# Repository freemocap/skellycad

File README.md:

# SkellyCAD

CAD, eye-tracker hardware, camera electronics and learning projects.
Start with a project below; its README distinguishes selected assemblies,
review candidates and available print packages.

| Project | Start here |
| --- | --- |
| Eye trackers | [Mouse, rat, marmoset and human](designs/eye-tracker/README.md) |
| Camera modules | [Pupil reference and camera development](designs/cameras/README.md) |
| Capture enclosure | [Frame and capture studies](designs/enclosure/README.md) |
| UltraSkelly mounts | [Camera bracket and Pi 5 stack mount](designs/ultraskelly/README.md) |
| Preserved Mouse Hats | [Historical designs and replay](designs/mouse-hats/README.md) |
| CAD Foundations | [FreeCAD lessons](designs/cad-foundations/README.md) |
| KiCad Foundations | [Electronics lessons](designs/kicad-foundations/README.md) |

[Working guide](docs/organization-guide.md) · [Setup and validation](docs/development.md) ·
[Version control](docs/version-control.md) · [Citations](CITATIONS.md)

The preferred Pupil geometry is the [complete R08 module](designs/cameras/pupil-core-eye/README.md).
Historical assemblies retain their pinned geometry and matched parts.

[Repository cleanup plan](docs/repository-organization.md) ·
[Cleanup and preservation record](docs/migration/repo-cleanup-2026-10-31/README.md) ·
[Original import record](docs/migration/README.md)

Local runtimes stay in `.cad-tools/`; working runs go to `generated/`.
The original `old-cad-playground/` remains untouched for the user's migration review.

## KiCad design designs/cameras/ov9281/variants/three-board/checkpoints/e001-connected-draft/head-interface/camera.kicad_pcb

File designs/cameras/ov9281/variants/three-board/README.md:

# OV9281 three-board

**E01** is a connected electrical draft with unrouted placement and a matched mechanical assembly. It is not accepted for manufacture.

- [Source](src) contains the retained implementation for this configuration.
- [Matched E01 files](checkpoints/e001-connected-draft).
- [Native complete assembly](checkpoints/e001-connected-draft/THREE-BOARD-E01.FCStd) · [Selection/review record](review-model.json).

Use [the working guide](../../../../../docs/organization-guide.md) for isolated replay. Historical commands retain their original paths; run them in the prepared workspace. Use `--current --source designs/cameras/ov9281/variants/three-board/src` when preparing a fresh workspace to include edits from this variant's `src/`.

Keep the native assembly, matching parts, electronics contracts and validation scope together. A saved model or successful geometry check does not demonstrate physical fit.

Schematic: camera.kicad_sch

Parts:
C7, C8, C10, C12, C13, C18, C19, C21, C33, C401, C403, C405, C423, C424, C425, C426: 1u; C_0603_1608Metric; MPN GRM188R71C105KA12D
C9, C14, C15, C16, C17, C20, C408, C411, C414, C417, C418: 100n; C_0402_1005Metric; MPN GRM155R71C104KA88D
C402, C404, C406, C409, C412, C415: 10n; C_0402_1005Metric; MPN GRM155R71C103KA01D
C407, C410, C413: 10u; C_0805_2012Metric; MPN GRM21BR61A106KE19L
C416: 22n; C_0402_1005Metric; MPN GRM155R71H223KA12D
C419, C420: 100n/50V; C_0402_1005Metric; MPN GRM155R71H104KE14D
C421: 4.7u; C_0603_1608Metric; MPN GRM188R61A475KE15D
C422: 22u; C_0805_2012Metric; MPN GRM21BR61A226ME44L
D201, D202: AP1608F3C; Kingbright_AP1608F3C_R09; MPN AP1608F3C
D203, D204: TPD1E01B04 / 0.20pF typ; D_0402_1005Metric; MPN TPD1E01B04DPYR
FB401, FB402, FB403: 120R@100MHz; L_0603_1608Metric; MPN BLM18SG121TN1D
J201: TETHER: 1=5V 2=N 3=P 4=GND; NOT USB; JST_SH_SM04B-SRSS-TB_1x04-1MP_P1.00mm_Horizontal; MPN SM04B-SRSS-TB(LF)(SN)
L1, L2, L3: 3.3u; L_0805_2012Metric; MPN MLP2012S3R3MT0S1
L202: 2.2u / 3.3 A Isat; Murata_DFE252012F_R11; MPN DFE252012F-2R2M=P2
Q201: PMZB200UNE; SOT-883; MPN PMZB200UNEYL
R7: 0; R_0402_1005Metric; MPN RC0402JR-070RL; not fitted
R8, R9: 0; R_0402_1005Metric; MPN RC0402JR-070RL
R201, R202, R203: 2.2k; R_0402_1005Metric; MPN RC0402FR-072K2L
R204, R407, R409: 100k; R_0402_1005Metric; MPN RC0402FR-07100KL
R401, R402, R405: 10k; R_0402_1005Metric; MPN RC0402FR-0710KL
R403, R404: 4.7k; R_0402_1005Metric; MPN RC0402FR-074K7L
R406: 40.2k; R_0402_1005Metric; MPN RC0402FR-0740K2L
R408: 200k; R_0402_1005Metric; MPN RC0402FR-07200KL
TP201: Shield termination; TestPoint_Pad_1.0x1.0mm; MPN PCB solder land
U1: OV9281; MPN OV09281-H64A
U6: TLV73312PDQNR; Texas_X2SON-4_1x1mm_P0.65mm; MPN TLV73312PDQNR
U7: TLV73328PDQNR; Texas_X2SON-4_1x1mm_P0.65mm; MPN TLV73328PDQNR
U201: DS90UB953-Q1; TI_RHB0032P_E01; MPN DS90UB953TRHBRQ1
U202: TLV62569DRLR; TI_DRL0006A_R11; MPN TLV62569DRLR
Y1: SG-210STF 24.0000ML; Epson_SG210STF_2.5x2.0mm_R09; MPN X1G004171003100

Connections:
CAM_L_CLK_N: U1.H4 (MDCN), U201.6 (CSI_CLKN)
CAM_L_CLK_P: U1.G4 (MDCP), U201.5 (CSI_CLKP)
CAM_L_D0_N: U1.H3 (MDN0), U201.4 (CSI_D0N)
CAM_L_D0_P: U1.G3 (MDP0), U201.3 (CSI_D0P)
CAM_L_D1_N: U1.F5 (MD1N), U201.2 (CSI_D1N)
CAM_L_D1_P: U1.G5 (MDP1), U201.1 (CSI_D1P)
CAM_NRST_1V8: R401.1, U1.A5 (XSHUTDOWN), U201.17 (GPIO0)
GND: C7.2, C8.2, C9.2, C10.2, C12.2, C13.2, C14.2, C15.2, C16.2, C17.2, C18.2, C19.2, C20.2, C21.2, C33.2, C401.2, C402.2, C403.2, C404.2, C405.2, C406.2, C407.2, C408.2, C409.2, C410.2, C411.2, C412.2, C413.2, C414.2, C415.2, C417.2, C418.2, C421.2, C422.2, C423.2, C424.2, C425.2, C426.2, D203.2 (IO_GND), D204.2 (IO_GND), J201.4, Q201.2 (S), R8.2, R204.2, R401.2, R402.2, R405.2, R406.2, R409.2, TP201.1, U1.A3 (DOGND), U1.A7 (DOGND), U1.B2 (DOGND), U1.C8 (AGND), U1.D2 (AGND), U1.E3 (EGND), U1.E5 (EGND), U1.E6 (TM), U1.F1 (DOGND), U1.F4 (DOGND), U1.F6 (DOGND), U1.F8 (AGND), U1.G2 (DOGND), U1.H7 (AGND), U6.2 (GND), U6.5 (EP), U7.2 (GND), U7.5 (EP), U201.7 (RES0), U201.33 (EP), U202.2 (GND), Y1.2 (GND)
H1V2: C423.1, L1.1, U6.1 (VOUT)
H1V8: C33.1, C422.1, C424.1, FB401.1, FB402.1, FB403.1, L2.1, L202.2, R403.1, R404.1, R407.1, R408.1, U6.3 (EN), U6.4 (VIN), Y1.1 (EN), Y1.4 (VDD)
H2V8: C425.1, L3.1, U7.1 (VOUT)
H5V: C421.1, C426.1, J201.1, R201.1, R202.1, U7.3 (EN), U7.4 (VIN), U202.3 (VIN), U202.5 (EN)
IR_A1: D201.2 (A), R201.2
IR_A2: D202.2 (A), R202.2
IR_GATE: Q201.1 (G), R203.2, R204.1
IR_K: D201.1 (K), D202.1 (K), Q201.3 (D)
LINK_N: C420.2, D204.1 (IO), J201.2
LINK_P: C419.2, D203.1 (IO), J201.3
M1_AVDD: C18.1, C19.1, C20.1, L3.2, R9.2, U1.B8 (AVDD), U1.C1 (AVDD), U1.G7 (AVDD), U1.G8 (AVDD)
M1_CAM_SCL_1V8: R403.2, U1.E4 (SCL), U201.24 (I2C_SCL)
M1_CAM_SDA_1V8: R404.2, U1.A4 (SDA), U201.23 (I2C_SDA)
M1_DOVDD: C13.1, C15.1, C16.1, L2.2, R7.1, U1.B7 (DOVDD), U1.D3 (DOVDD), U1.H2 (DOVDD), U1.H6 (DOVDD)
M1_DVDD: C9.1, C12.1, C14.1, L1.2, U1.A2 (DVDD), U1.B1 (DVDD), U1.B3 (DVDD), U1.C5 (DVDD), U1.D8 (DVDD), U1.F2 (DVDD), U1.F3 (EVDD), U1.G1 (DVDD), U1.G6 (DVDD), U1.H5 (EVDD)
M1_MCLK: U1.E2 (XVCLK), Y1.3 (OUT)
M1_PVDD: C17.1, R9.1, U1.D5 (PVDD)
M1_SID: R7.2, R8.1, U1.E1 (SID)
M1_VH: C21.1, U1.E8 (VH)
M1_VN1: C7.1, U1.D7 (VN1)
M1_VN2: C8.1, U1.E7 (VN2)
M1_VN3: C10.1, U1.F7 (VN3)
M1_VSYNC_1V8_M: R402.1, U1.B5 (FSIN/VSYNC)
SER_DOUT_N: C420.1, U201.13 (DOUT_N)
SER_DOUT_P: C419.1, U201.14 (DOUT_P)
SER_DRV_CAP: C410.1, C411.1, C412.1, U201.15 (VDDDRV_CAP)
SER_D_CAP: C413.1, C414.1, C415.1, U201.26 (VDDD_CAP)
SER_IDX: R406.1, U201.19 (CLK_OUT_IDX)
SER_LED_PWM: R203.1, U201.18 (GPIO1)
SER_LPF1: C416.1, U201.9 (LPF1)
SER_LPF2: C417.1, U201.12 (LPF2)
SER_MODE: R405.1, U201.21 (MODE)
SER_PDB: C418.1, R407.2, U201.8 (PDB)
SER_PLL_CAP: C407.1, C408.1, C409.1, U201.10 (VDDPLL_CAP)
SER_VDDD: C401.1, C402.1, FB401.2, U201.25 (VDDD)
SER_VDDDRV: C403.1, C404.1, FB402.2, U201.16 (VDDDRV)
SER_VDDPLL: C405.1, C406.1, C416.2, FB403.2, U201.11 (VDDPLL)
U202_FB: R408.2, R409.1, U202.1 (FB)
U202_SW: L202.1, U202.4 (SW)

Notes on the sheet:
THREE-BOARD E01 / HEAD-INTERFACE / CONNECTED ELECTRICAL DRAFT
Pins and matching net labels define connectivity. Unrouted; procurement, optics, cable and hardware qualification remain open.
Active circuitry
Supporting parts / references match BOM and PCB / no implicit connections

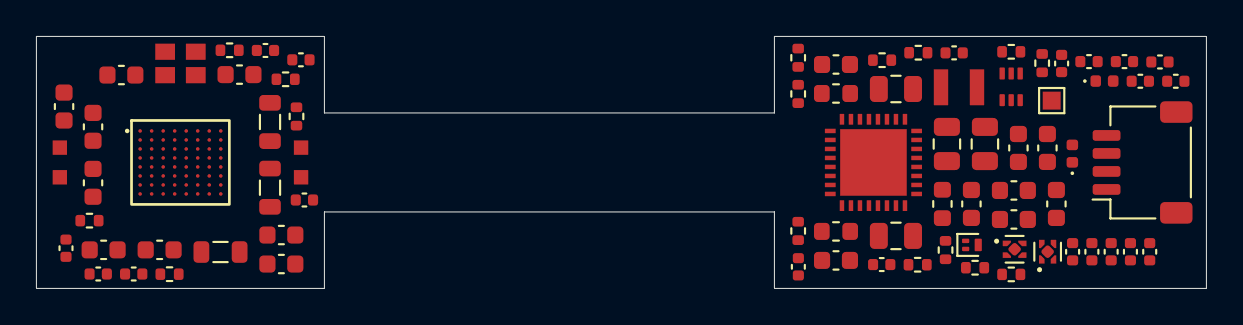
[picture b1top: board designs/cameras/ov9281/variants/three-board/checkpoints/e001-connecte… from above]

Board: 4 copper layers, 65.0 x 14.0 mm, 77 parts (0 on the bottom side), 47 nets, no tracks yet.

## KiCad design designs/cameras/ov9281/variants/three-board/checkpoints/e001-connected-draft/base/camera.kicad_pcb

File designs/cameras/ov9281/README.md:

# OV9281 camera development

| Configuration | Status and entry point |
| --- | --- |
| [Slim-flex](variants/slim-flex/README.md) | Preserved R11 routed candidate; R08 remains the historical electrical selection. |
| [Three-board](variants/three-board/README.md) | E01 connected electrical draft and matched mechanical assembly; boards remain unrouted. |

Neither configuration is an accepted manufacturing release or demonstrated
working camera. The nominal mass targets and unresolved electrical/optical gates
remain in the variant records.

[Shared earlier investigations](history/README.md) · [Supplied references](references) ·
[Pre-cleanup overview](history/overview-before-cleanup.md)

[Shared utilities](shared/README.md) · [Development roadmap](ROADMAP.md)

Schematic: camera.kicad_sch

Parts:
C101, C102: 16p; C_0402_1005Metric; MPN GRM1555C1H160JA01D
C103, C110, C111, C112, C113, C114, C115, C116, C117, C118, C119, C120, C121, C122, C128, C129, C130, C132, C135, C607, C612, C618, C620, C622, C624, C627: 100n; C_0402_1005Metric; MPN GRM155R71C104KA88D
C104, C125, C126, C127, C133, C604, C609, C615, C628, C629: 1u; C_0603_1608Metric; MPN GRM188R71C105KA12D
C105, C108, C136, C601, C602, C617, C619, C621, C623: 4.7u; C_0603_1608Metric; MPN GRM188R61A475KE15D
C106, C109, C123, C124, C603: 22u; C_0805_2012Metric; MPN GRM21BR61A226ME44L
C107: 22p; C_0402_1005Metric; MPN GRM1555C1H220JA01D
C131, C134, C605, C608, C610, C613, C616: 10n; C_0402_1005Metric; MPN GRM155R71C103KA01D
C606, C611, C614: 10u; C_0805_2012Metric; MPN GRM21BR61A106KE19L
C625, C626: 100n/50V; C_0402_1005Metric; MPN GRM155R71H104KE14D
D301, D302: TPD1E01B04 / 0.20pF typ; D_0402_1005Metric; MPN TPD1E01B04DPYR
FB601, FB602, FB603: 120R@100MHz; L_0603_1608Metric; MPN BLM18SG121TN1D
J101: USB / JST SH / 1VBUS 2DM 3DP 4GND; JST_SH_SM04B-SRSS-TB_1x04-1MP_P1.00mm_Horizontal; MPN SM04B-SRSS-TB(LF)(SN)
J103: PROGRAM / RESET pads; ProgrammingPads_5x1mm_P1.5mm; MPN PCB programming lands
J301: TETHER: 1=5V 2=N 3=P 4=GND; NOT USB; JST_SH_SM04B-SRSS-TB_1x04-1MP_P1.00mm_Horizontal; MPN SM04B-SRSS-TB(LF)(SN)
L101, L102, L302: 2.2u / 3.3 A Isat; Murata_DFE252012F_R11; MPN DFE252012F-2R2M=P2
Q301, Q302: PMZB200UNE; SOT-883; MPN PMZB200UNEYL
R101, R102, R103, R104, R605, R609, R610, R612, R615: 10k; R_0402_1005Metric; MPN RC0402FR-0710KL
R105, R106: 499k; R_0402_1005Metric; MPN RC0402FR-07499KL
R107: 453k; R_0402_1005Metric; MPN RC0402FR-07453KL
R108, R601, R602, R604, R613, R614: 100k; R_0402_1005Metric; MPN RC0402FR-07100KL
R109, R110: 0; R_0402_1005Metric; MPN RC0402JR-070RL
R111: 4.02k; R_0402_1005Metric; MPN RC0402FR-074K02L
R113, R115, R608: 4.7k; R_0402_1005Metric; MPN RC0402FR-074K7L
R603: 200k; R_0402_1005Metric; MPN RC0402FR-07200KL
R606: 78.7k; R_0402_1005Metric; MPN RC0402FR-0778K7L
R607: 97.6k; R_0402_1005Metric; MPN RC0402FR-0797K6L
R611: 80.6k; R_0402_1005Metric; MPN RC0402FR-0780K6L
TP301: Tether shield; TestPoint_Pad_1.0x1.0mm; MPN PCB solder land
TP302: REGULATED 5V INPUT; TestPoint_Pad_1.0x1.0mm; MPN PCB solder land
TP303: POWER RETURN; TestPoint_Pad_1.0x1.0mm; MPN PCB solder land
U101: ESP32-P4NRW16X / v3.x; ESP32-P4; MPN ESP32-P4NRW16X
U102: W25Q32JVUUIQ / 4 MB; Winbond_USON-8-2EP_3x4mm_P0.8mm_EP0.2x0.8mm; MPN W25Q32JVUUIQ TR
U103, U104, U302: TLV62569DRLR; TI_DRL0006A_R11; MPN TLV62569DRLR
U105: USBLC6-2P6; SOT-666; MPN USBLC6-2P6
U301: DS90UB954-Q1 / internal LDOs; TI_RGZ0048B_E01; MPN DS90UB954TRGZRQ1
U303: TPS2553 / current-limited head power; TI_DRV0006A_E01; MPN TPS2553DRVR
Y101: 40 MHz / CL 10pF; ECS_ECX1637B2_R11; MPN ECS-400-10-37B2-CKM-TR
Y301: SG-210STF 25.0000ML / 1.8V; Epson_SG210STF_2.5x2.0mm_R09; MPN SG-210STF 25.0000ML

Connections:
+3V3: C105.1, C109.1, C110.1, C111.1, C114.1, C115.1, C117.1, C118.1, C120.1, C121.1, C122.1, C123.1, C134.1, C135.1, C136.1, C604.1, C605.1, C609.1, C610.1, L102.2, R102.1, R103.1, R104.1, R107.1, R113.1, R115.1, R608.1, R609.1, R612.1, R615.1, U101.9 (VDD_LP), U101.21 (VDD_IO_0), U101.51 (VDD_USBPHY), U101.62 (VDD_IO_4), U101.75 (VDD_LDO), U101.77 (VDD_DCDCC), U101.85 (VDD_IO_5), U101.96 (VDD_IO_6), U101.101 (VDD_ANA), U101.102 (VDD_BAT), U103.3 (VIN), U301.7 (VDDIO), U301.29 (VDDIO)
B5V: C601.1, C602.1, C628.1, TP302.1, U104.3 (VIN), U104.5 (EN), U302.3 (VIN), U302.5 (EN), U303.6 (IN)
BASE_SCL: R113.2, U101.7 (GPIO7), U301.2 (SCL)
BASE_SDA: R115.2, U101.8 (GPIO8), U301.1 (SDA)
CAM_L_CLK_N: U101.45 (CSI_CLKN), U301.11 (CSI_CLK0N)
CAM_L_CLK_P: U101.44 (CSI_CLKP), U301.12 (CSI_CLK0P)
CAM_L_D0_N: U101.42 (CSI_DATAN0), U301.13 (CSI_D0N)
CAM_L_D0_P: U101.43 (CSI_DATAP0), U301.14 (CSI_D0P)
CAM_L_D1_N: U101.46 (CSI_DATAN1), U301.15 (CSI_D1N)
CAM_L_D1_P: U101.47 (CSI_DATAP1), U301.16 (CSI_D1P)
FLASH_CLK: U101.32 (FLASH_CK), U102.6 (CLK)
FLASH_CS: R101.2, U101.27 (FLASH_CS), U102.1 (~CS)
FLASH_D: U101.33 (FLASH_D), U102.5 (DI/IO_{0})
FLASH_HOLD: U101.31 (FLASH_HOLD), U102.7 (~HOLD/~RESET/IO_{3})
FLASH_Q: U101.28 (FLASH_Q), U102.2 (DO/IO_{1})
FLASH_WP: U101.29 (FLASH_WP), U102.3 (~WP/IO_{2})
GND: C101.2, C102.2, C103.2, C104.2, C105.2, C106.2, C108.2, C109.2, C110.2, C111.2, C112.2, C113.2, C114.2, C115.2, C116.2, C117.2, C118.2, C119.2, C120.2, C121.2, C122.2, C123.2, C124.2, C125.2, C126.2, C127.2, C128.2, C129.2, C130.2, C131.2, C132.2, C133.2, C134.2, C135.2, C136.2, C601.2, C602.2, C603.2, C604.2, C605.2, C606.2, C607.2, C608.2, C609.2, C610.2, C611.2, C612.2, C613.2, C614.2, C615.2, C616.2, C617.2, C618.2, C619.2, C620.2, C621.2, C622.2, C623.2, C624.2, C627.2, C628.2, C629.2, D301.2 (IO_GND), D302.2 (IO_GND), J101.4, J103.1, J301.4, Q301.2 (S), Q302.2 (S), R106.2, R108.2, R111.2, R601.2, R602.2, R604.2, R605.2, R607.2, R611.2, R614.2, TP301.1, TP303.1, U101.105 (GND), U102.4 (GND), U102.9 (EP), U103.2 (GND), U104.2 (GND), U105.2 (GND), U301.6 (BISTEN), U301.44 (RES), U301.46 (VDD_SEL), U301.49 (EP), U302.2 (GND), U303.5 (GND), U303.7 (EP), Y101.2 (G), Y101.4 (G), Y301.2 (GND)
LINK_N: C626.1, D302.1 (IO), J301.2
LINK_P: C625.1, D301.1 (IO), J301.3
P4_BOOT: J103.4, R103.2, U101.66 (GPIO35)
P4_CSI_REXT: R111.1, U101.48 (CSI_REXT)
P4_DOWNLOAD_ENABLE: R104.2, U101.68 (GPIO36)
P4_EN: C104.1, J103.5, R102.2, U101.103 (CHIP_PU)
P4_EN_DCDC: U101.79 (EN_DCDC), U103.5 (EN)
P4_FB: C107.2, R105.2, R106.1, U101.78 (FB_DCDC), U103.1 (FB)
P4_FLASH_VDD: C103.1, C125.1, C128.1, R101.1, U101.30 (VDD_FLASH_IO), U101.71 (VDDO_FLASH), U102.8 (VCC)
P4_LDO4_UNUSED: C127.1, U101.74 (VDDO_4)
P4_MIPI_2V5: C131.1, C132.1, C133.1, U101.41 (VDD_MIPI_DPHY), U101.73 (VDDO_3)
P4_PSRAM_VDD: C126.1, C129.1, C130.1, U101.59 (VDD_PSRAM_0), U101.67 (VDD_PSRAM_1), U101.72 (VDDO_PSRAM)
P4_SW: L101.1, U103.4 (SW)
P4_UART_RX: J103.3, U101.70 (GPIO38)
P4_UART_TX: J103.2, U101.69 (GPIO37)
P4_VDD_HP: C106.1, C107.1, C112.1, C113.1, C116.1, C119.1, C124.1, L101.2, R105.1, U101.26 (VDD_HP_0), U101.54 (VDD_HP_1), U101.76 (VDD_HP_2), U101.91 (VDD_HP_3)
P4_XTAL_N: C102.1, U101.99 (XTAL_N), Y101.3
P4_XTAL_P: C101.1, U101.100 (XTAL_P), Y101.1
RX1V8: C603.1, C627.1, FB601.1, FB602.1, FB603.1, L302.2, R603.1, R606.1, R610.1, Y301.4 (VDD)
RX_CLK_DISABLE: Q301.1 (G), R609.2, U101.10 (GPIO9)
RX_CLK_OE: Q301.3 (D), R610.2, Y301.1 (EN)
RX_CSI_CAP: C619.1, C620.1, U301.20 (VDD11_CSI)
RX_D_CAP: C617.1, C618.1, U301.3 (VDD11_D)
RX_FPD0_CAP: C621.1, C622.1, U301.43 (VDD11_FPD0)
RX_FPD1_CAP: C623.1, C624.1, U301.34 (VDD11_FPD1)
RX_IDX: R605.1, U301.35 (IDX)
RX_INT_N: R608.2, U101.14 (GPIO13), U301.25 (GPIO3_INTB)
RX_IN_N: C626.2, U301.42 (RIN0N)
RX_IN_P: C625.2, U301.41 (RIN0P)
RX_LOCK: U101.11 (GPIO10), U301.48 (LOCK)
RX_MODE: R606.2, R607.1, U301.37 (MODE)
RX_PASS: U101.12 (GPIO11), U301.47 (PASS)
RX_PDB: R601.1, U101.6 (GPIO6), U301.30 (PDB)
RX_REFCLK: U301.5 (XIN_REFCLK), Y301.3 (OUT)
RX_VDD18_CSI: C615.1, C616.1, FB601.2, U301.17 (VDD18_CSI)
RX_VDD18_FPD: C606.1, C607.1, C611.1, C612.1, FB602.2, U301.31 (VDD18_FPD1), U301.40 (VDD18_FPD0)
RX_VDD18_P: C608.1, C613.1, C614.1, FB603.2, U301.36 (VDD18_P1), U301.45 (VDD18_P0)
SYS_FB: R107.2, R108.1, U104.1 (FB)
SYS_SW: L102.1, U104.4 (SW)
TETHER_5V: C629.1, J301.1, U303.1 (OUT)
TETHER_EN: R602.1, U101.5 (GPIO5), U303.4 (EN)
TETHER_FAULT_N: R612.2, U101.13 (GPIO12), U303.3 (FAULT_N)
TETHER_ILIM: R611.1, U303.2 (ILIM)
U302_FB: R603.2, R604.1, U302.1 (FB)
U302_SW: L302.1, U302.4 (SW)
USB_DM: J101.2, R109.1, U105.1 (I/O1), U105.6 (I/O1)
USB_DM_CHIP: R109.2, U101.49 (USB-DM)
USB_DP: J101.3, R110.1, U105.3 (I/O2), U105.4 (I/O2)
USB_DP_CHIP: R110.2, U101.50 (USB-DP)
USB_PRESENT_N: Q302.3 (D), R615.2, U101.17 (GPIO16/ADC1_CHANNEL0)
USB_VBUS: C108.1, J101.1, R613.1, U105.5 (VBUS)
USB_VBUS_GATE: Q302.1 (G), R613.2, R614.1

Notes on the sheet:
THREE-BOARD E01 / BASE / CONNECTED ELECTRICAL DRAFT
Pins and matching net labels define connectivity. Unrouted; procurement, optics, cable and hardware qualification remain open.
Active circuitry
Supporting parts / references match BOM and PCB / no implicit connections

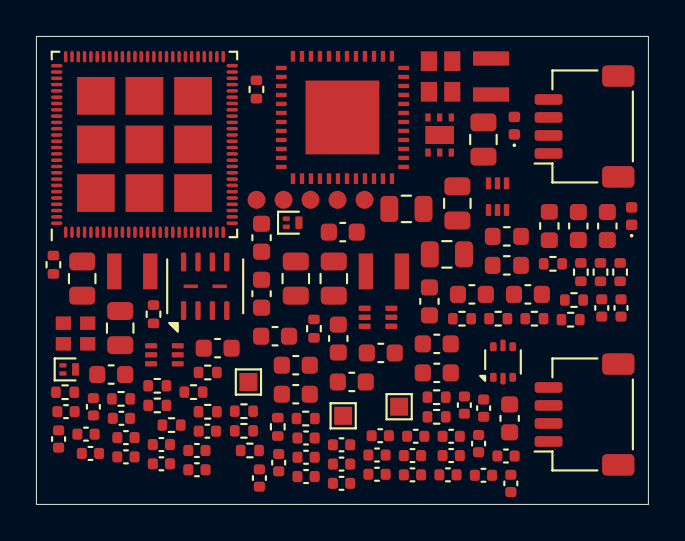
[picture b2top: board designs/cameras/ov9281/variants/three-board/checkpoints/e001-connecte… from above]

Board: 4 copper layers, 34.0 x 26.0 mm, 119 parts (0 on the bottom side), 69 nets, no tracks yet.

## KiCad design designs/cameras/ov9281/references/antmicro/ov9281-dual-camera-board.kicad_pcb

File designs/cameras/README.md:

# Camera catalog

| Camera | Role and status |
| --- | --- |
| [Pupil Core eye](pupil-core-eye/README.md) | Selected complete R08 mock-up, optical datum and retained geometry studies. |
| [Inherited Pupil fit profile](pupil-core-eye-inherited/README.md) | Historical approximate envelope used by preserved assemblies. |
| [OV9281](ov9281/README.md) | Slim-flex and three-board engineering work; no demonstrated working camera. |
| [OG0TC / OC0TC](og0tc/README.md) | Preserved earlier direction, superseded by OV9281 development. |

Use `shared.camera.add_camera` for new Pupil geometry. Keep the complete module
and optical datum together. Existing species checkpoints retain their selections.

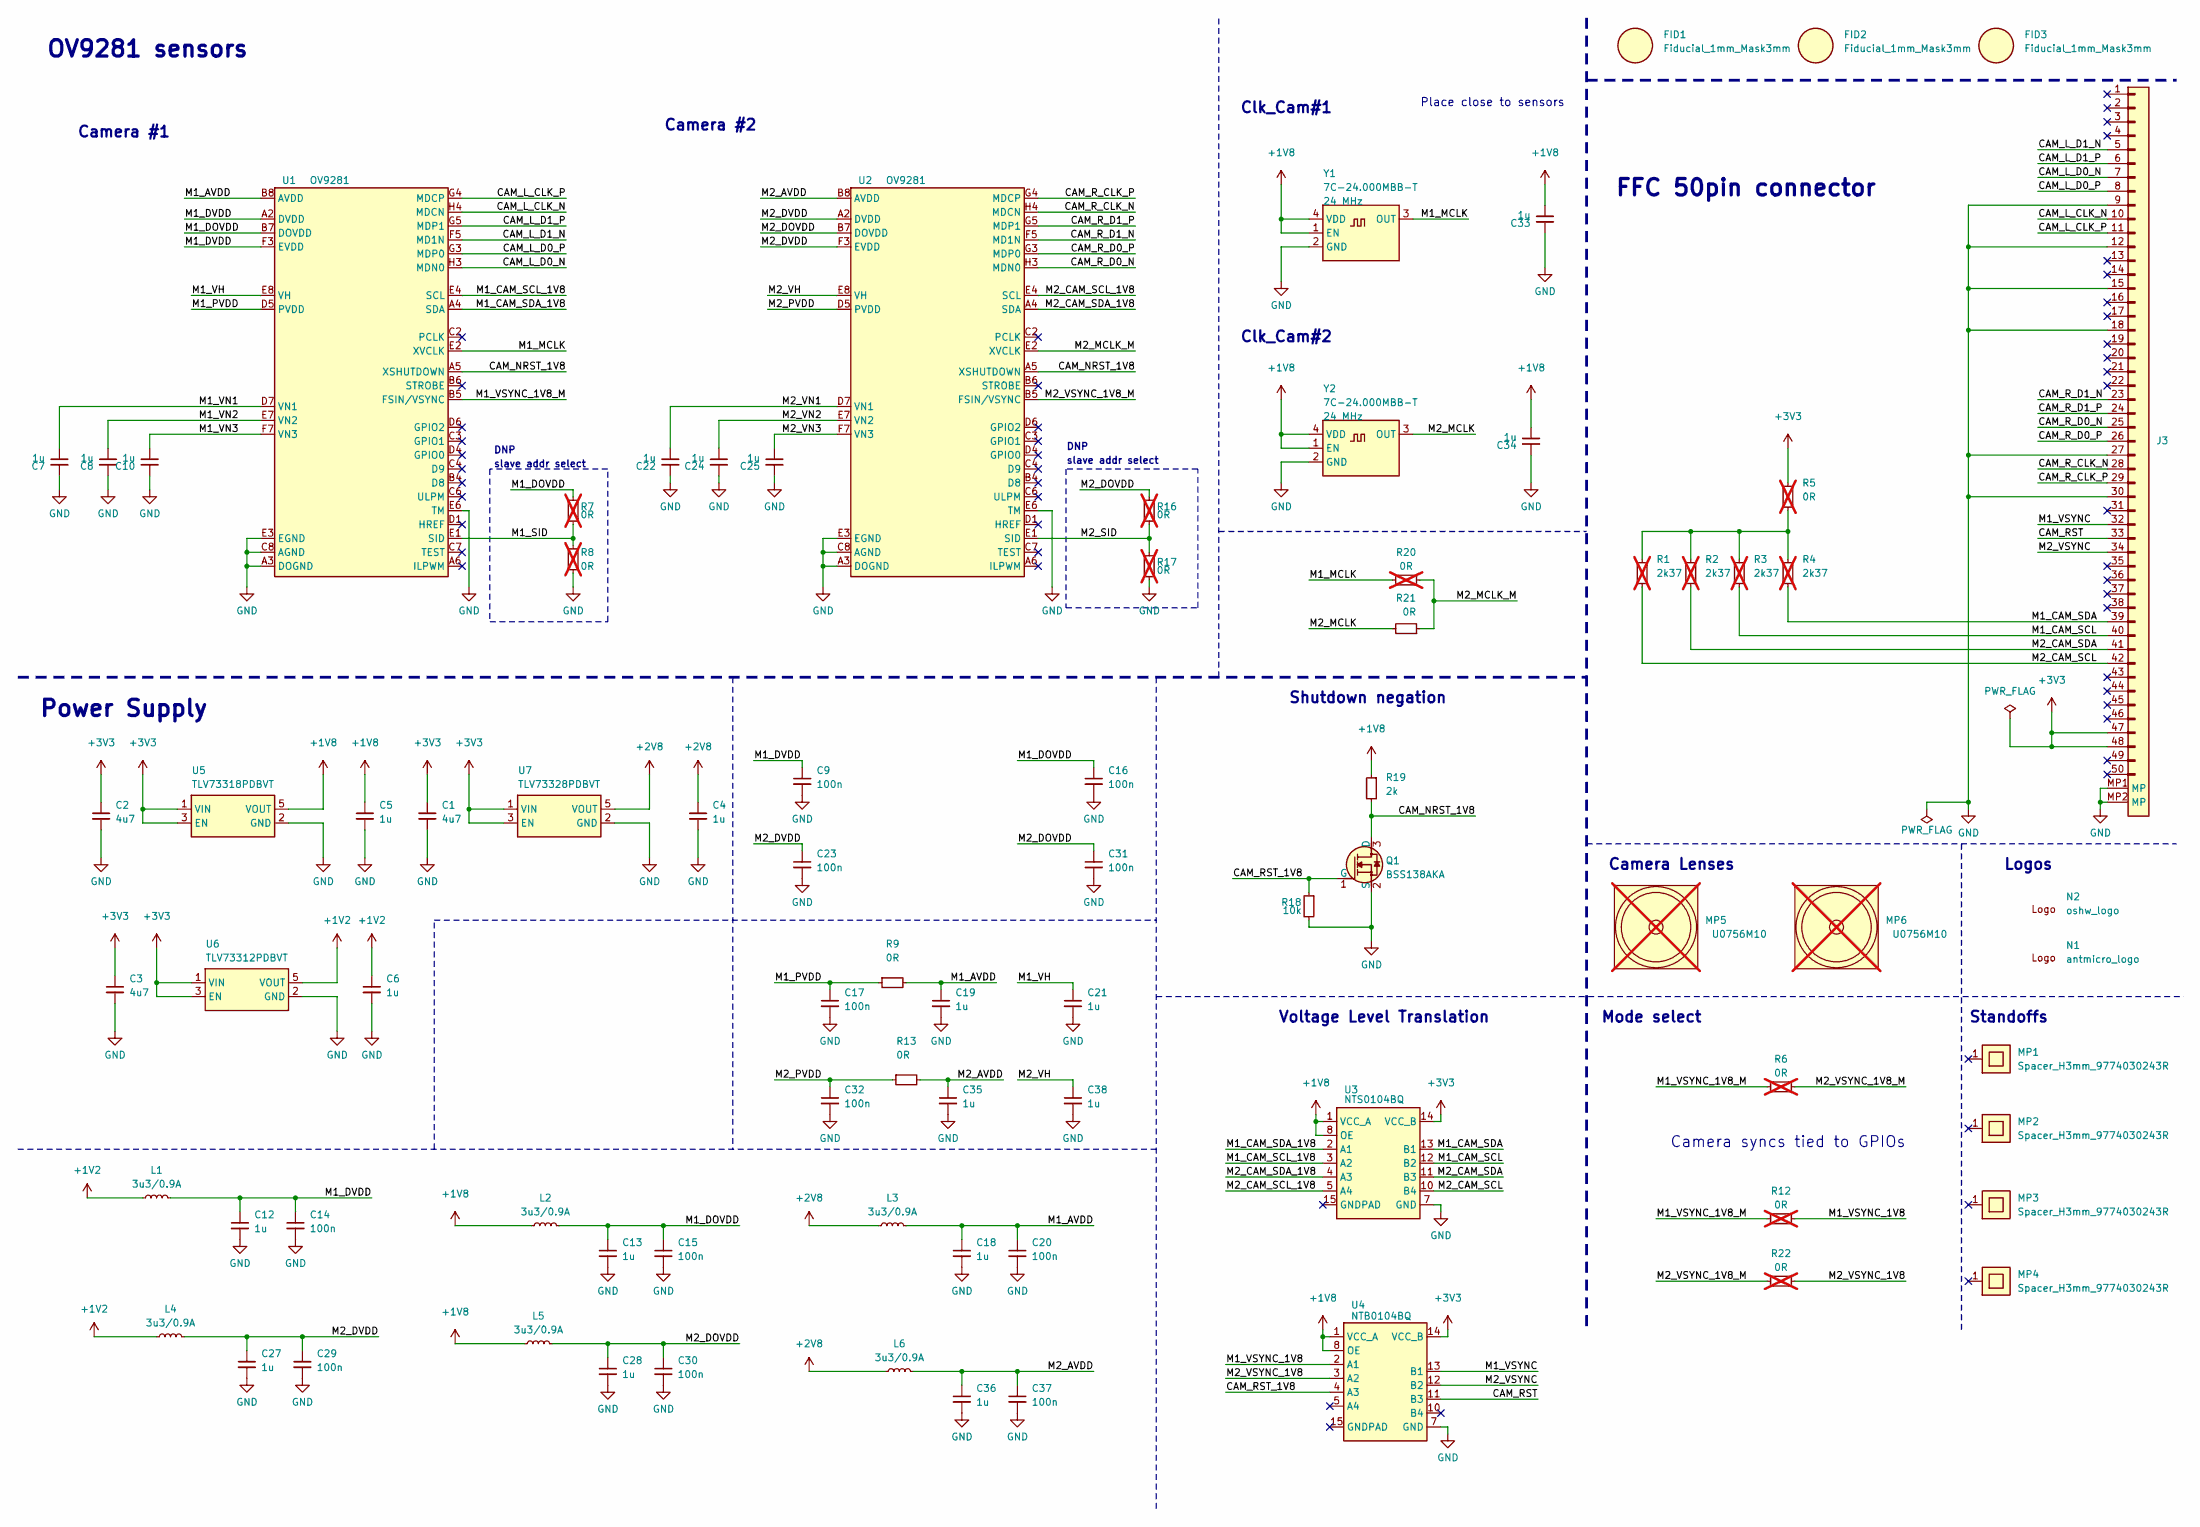
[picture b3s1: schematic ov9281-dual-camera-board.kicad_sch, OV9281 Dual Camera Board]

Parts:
C1, C2, C3: C_4u7_0805; C_0805_2012Metric; MPN 0805X475K250CT
C4, C5, C6, C7, C8, C10, C12, C13, C18, C19, C21, C22, C24, C25, C27, C28, C33, C34, C35, C36, C38: C_1u_0603; C_0603_1608Metric; MPN 0603YD105KAT2A
C9, C14, C15, C16, C17, C20, C23, C29, C30, C31, C32, C37: C_100n_6V3_0402; C_0402_1005Metric; MPN 0402X104K6R3CT
FID1, FID2, FID3: Fiducial_1mm_Mask3mm
J3: Conn_FFC_WE_68715014522_TWO-SIDES; Conn_FFC_WE_68715014x22_ALT; MPN 68715014522
L1, L2, L3, L4, L5, L6: MLP2012S3R3MT; L_0805_2012Metric; MPN MLP2012S3R3MT
MP1, MP2, MP3, MP4: Spacer_H3mm_9774030243R; Spacer_Drill3mm_H3mm_9774030243R; MPN 9774030243R
MP5, MP6: Camera_Lens_20mm; MPN U0756M10; not fitted
N1: antmicro_logo; antmicro-logo_scaled_20mm
N2: oshw_logo; oshw-logo
Q1: BSS138AKA; SOT-23-3; MPN BSS138AKA
R1, R2, R3, R4: R_2k37_0402; R_0402_1005Metric; Tolerance 1%; MPN CR0402-FX-2371GLF; not fitted
R5, R6, R7, R8, R12, R16, R17, R20, R22: R_0R_0402; R_0402_1005Metric; MPN ERJ2GE0R00X; not fitted
R9, R13, R21: R_0R_0402; R_0402_1005Metric; MPN ERJ2GE0R00X
R18: R_10k_0402; R_0402_1005Metric; Tolerance 1%; MPN CR0402-FX-1002GLF
R19: R_2k_0402; R_0402_1005Metric; Tolerance 1%; MPN CR0402-FX-2001GLF
U1, U2: ImageSensor_OV9281; OV9281; MPN OV9281
U3: NTS0104BQ; DHVQFN-14-1EP_2.5x3mm; MPN NTS0104BQ
U4: NTB0104BQ; DHVQFN-14-1EP_2.5x3mm; MPN NTB0104BQ
U5: TLV73318PDBVT; SOT-23-5; MPN TLV73318PDBVT
U6: TLV73312PDBVT; SOT-23-5; MPN TLV73312PDBVT
U7: TLV73328PDBVT; SOT-23-5; MPN TLV73328PDBVT
Y1, Y2: 7C-24.000MBB-T; Oscillator_SMD_TXC_7C_5x3.2x1.2mm; MPN 7C-24.000MBB-T

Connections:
+1V2: C6.1, L1.1, L4.1, U6.5 (VOUT)
+1V8: C5.1, C33.1, C34.1, L2.1, L5.1, R19.1, U3.1 (VCC_A), U3.8 (OE), U4.1 (VCC_A), U4.8 (OE), U5.5 (VOUT), Y1.1 (EN), Y1.4 (VDD), Y2.1 (EN), Y2.4 (VDD)
+2V8: C4.1, L3.1, L6.1, U7.5 (VOUT)
+3V3: C1.1, C2.1, C3.1, J3.47, J3.48, R5.1, U3.14 (VCC_B), U4.14 (VCC_B), U5.1 (VIN), U5.3 (EN), U6.1 (VIN), U6.3 (EN), U7.1 (VIN), U7.3 (EN)
/CAM_L_CLK_N: J3.10, U1.H4 (MDCN)
/CAM_L_CLK_P: J3.11, U1.G4 (MDCP)
/CAM_L_D0_N: J3.7, U1.H3 (MDN0)
/CAM_L_D0_P: J3.8, U1.G3 (MDP0)
/CAM_L_D1_N: J3.5, U1.F5 (MD1N)
/CAM_L_D1_P: J3.6, U1.G5 (MDP1)
/CAM_NRST_1V8: Q1.3 (D), R19.2, U1.A5 (XSHUTDOWN), U2.A5 (XSHUTDOWN)
/CAM_RST: J3.33, U4.11 (B3)
/CAM_RST_1V8: Q1.1 (G), R18.1, U4.4 (A3)
/CAM_R_CLK_N: J3.28, U2.H4 (MDCN)
/CAM_R_CLK_P: J3.29, U2.G4 (MDCP)
/CAM_R_D0_N: J3.25, U2.H3 (MDN0)
/CAM_R_D0_P: J3.26, U2.G3 (MDP0)
/CAM_R_D1_N: J3.23, U2.F5 (MD1N)
/CAM_R_D1_P: J3.24, U2.G5 (MDP1)
/M1_AVDD: C18.1, C19.1, C20.1, L3.2, R9.2, U1.B8 (AVDD), U1.C1 (AVDD), U1.G7 (AVDD), U1.G8 (AVDD)
/M1_CAM_SCL: J3.40, R3.2, U3.12 (B2)
/M1_CAM_SCL_1V8: U1.E4 (SCL), U3.3 (A2)
/M1_CAM_SDA: J3.39, R4.2, U3.13 (B1)
/M1_CAM_SDA_1V8: U1.A4 (SDA), U3.2 (A1)
/M1_DOVDD: C13.1, C15.1, C16.1, L2.2, R7.1, U1.B7 (DOVDD), U1.D3 (DOVDD), U1.H2 (DOVDD), U1.H6 (DOVDD)
/M1_DVDD: C9.1, C12.1, C14.1, L1.2, U1.A2 (DVDD), U1.B1 (DVDD), U1.B3 (DVDD), U1.C5 (DVDD), U1.D8 (DVDD), U1.F2 (DVDD), U1.F3 (EVDD), U1.G1 (DVDD), U1.G6 (DVDD), U1.H5 (EVDD)
/M1_MCLK: R20.2, U1.E2 (XVCLK), Y1.3 (OUT)
/M1_PVDD: C17.1, R9.1, U1.D5 (PVDD)
/M1_SID: R7.2, R8.1, U1.E1 (SID)
/M1_VH: C21.1, U1.E8 (VH)
/M1_VN1: C7.1, U1.D7 (VN1)
/M1_VN2: C8.1, U1.E7 (VN2)
/M1_VN3: C10.1, U1.F7 (VN3)
/M1_VSYNC: J3.32, U4.13 (B1)
/M1_VSYNC_1V8: R12.2, U4.2 (A1)
/M1_VSYNC_1V8_M: R6.1, R12.1, U1.B5 (FSIN/VSYNC)
/M2_AVDD: C35.1, C36.1, C37.1, L6.2, R13.2, U2.B8 (AVDD), U2.C1 (AVDD), U2.G7 (AVDD), U2.G8 (AVDD)
/M2_CAM_SCL: J3.42, R1.2, U3.10 (B4)
/M2_CAM_SCL_1V8: U2.E4 (SCL), U3.5 (A4)
/M2_CAM_SDA: J3.41, R2.2, U3.11 (B3)
/M2_CAM_SDA_1V8: U2.A4 (SDA), U3.4 (A3)
/M2_DOVDD: C28.1, C30.1, C31.1, L5.2, R16.1, U2.B7 (DOVDD), U2.D3 (DOVDD), U2.H2 (DOVDD), U2.H6 (DOVDD)
/M2_DVDD: C23.1, C27.1, C29.1, L4.2, U2.A2 (DVDD), U2.B1 (DVDD), U2.B3 (DVDD), U2.C5 (DVDD), U2.D8 (DVDD), U2.F2 (DVDD), U2.F3 (EVDD), U2.G1 (DVDD), U2.G6 (DVDD), U2.H5 (EVDD)
/M2_MCLK: R21.2, Y2.3 (OUT)
/M2_MCLK_M: R20.1, R21.1, U2.E2 (XVCLK)
/M2_PVDD: C32.1, R13.1, U2.D5 (PVDD)
/M2_SID: R16.2, R17.1, U2.E1 (SID)
/M2_VH: C38.1, U2.E8 (VH)
/M2_VN1: C22.1, U2.D7 (VN1)
/M2_VN2: C24.1, U2.E7 (VN2)
/M2_VN3: C25.1, U2.F7 (VN3)
/M2_VSYNC: J3.34, U4.12 (B2)
/M2_VSYNC_1V8: R22.2, U4.3 (A2)
/M2_VSYNC_1V8_M: R6.2, R22.1, U2.B5 (FSIN/VSYNC)
GND: C1.2, C2.2, C3.2, C4.2, C5.2, C6.2, C7.2, C8.2, C9.2, C10.2, C12.2, C13.2, C14.2, C15.2, C16.2, C17.2, C18.2, C19.2, C20.2, C21.2, C22.2, C23.2, C24.2, C25.2, C27.2, C28.2, C29.2, C30.2, C31.2, C32.2, C33.2, C34.2, C35.2, C36.2, C37.2, C38.2, J3.9, J3.12, J3.15, J3.18, J3.27, J3.30, J3.MP1 (MP), J3.MP2 (MP), Q1.2 (S), R8.2, R17.2, R18.2, U1.A3 (DOGND), U1.A7 (DOGND), U1.B2 (DOGND), U1.C8 (AGND), U1.D2 (AGND), U1.E3 (EGND), U1.E5 (EGND), U1.E6 (TM), U1.F1 (DOGND), U1.F4 (DOGND), U1.F6 (DOGND), U1.F8 (AGND), U1.G2 (DOGND), U1.H7 (AGND), U2.A3 (DOGND), U2.A7 (DOGND), U2.B2 (DOGND), U2.C8 (AGND), U2.D2 (AGND), U2.E3 (EGND), U2.E5 (EGND), U2.E6 (TM), U2.F1 (DOGND), U2.F4 (DOGND), U2.F6 (DOGND), U2.F8 (AGND), U2.G2 (DOGND), U2.H7 (AGND), U3.7 (GND), U4.7 (GND), U5.2 (GND), U6.2 (GND), U7.2 (GND), Y1.2 (GND), Y2.2 (GND)
unnamed: R1.1, R2.1, R3.1, R4.1, R5.2

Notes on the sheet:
Voltage Level Translation
FFC 50pin connector
slave addr select
Power Supply
Place close to sensors
Shutdown negation
DNP
Clk_Cam#2
Camera #1
Camera Lenses
Camera #2
Standoffs
Mode select
Logos
Camera syncs tied to GPIOs
OV9281 sensors
Clk_Cam#1

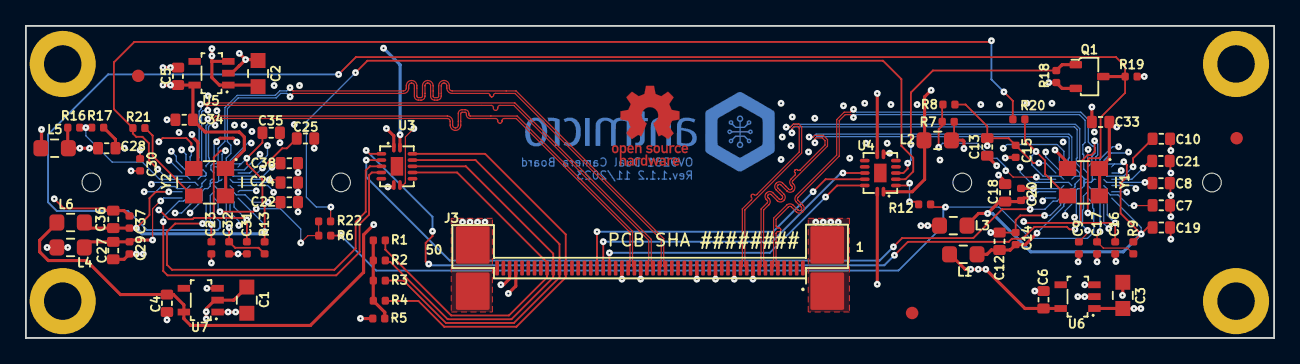
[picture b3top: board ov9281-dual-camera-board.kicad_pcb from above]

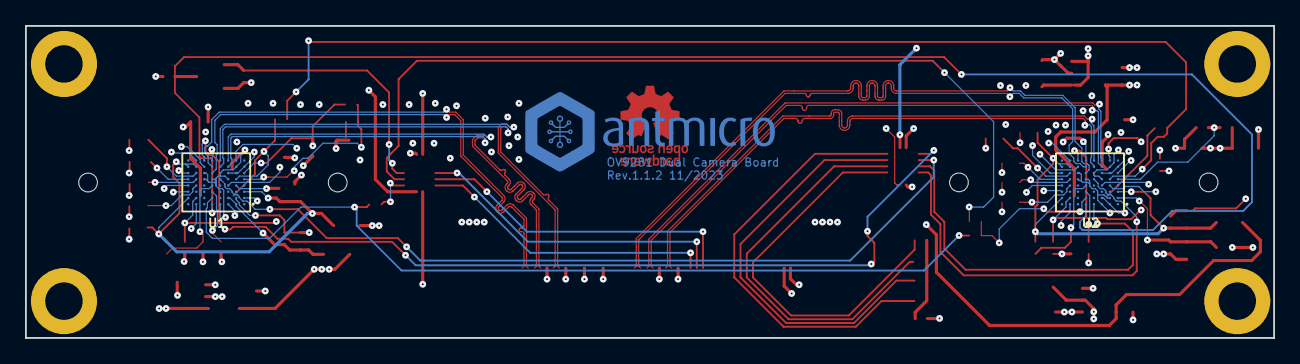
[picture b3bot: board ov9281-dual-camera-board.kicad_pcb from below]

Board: 4 copper layers, 100.0 x 25.0 mm, 82 parts (5 on the bottom side), 56 nets.

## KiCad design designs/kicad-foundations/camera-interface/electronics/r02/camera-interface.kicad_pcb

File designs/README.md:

# Design catalog

Use the [repository project catalog](../README.md) for current entry points.
Eye trackers are grouped by animal and variant. Camera modules have a shared
catalog; enclosure and UltraSkelly mount work are independent. Mouse Hats and
both foundations courses retain their established paths.

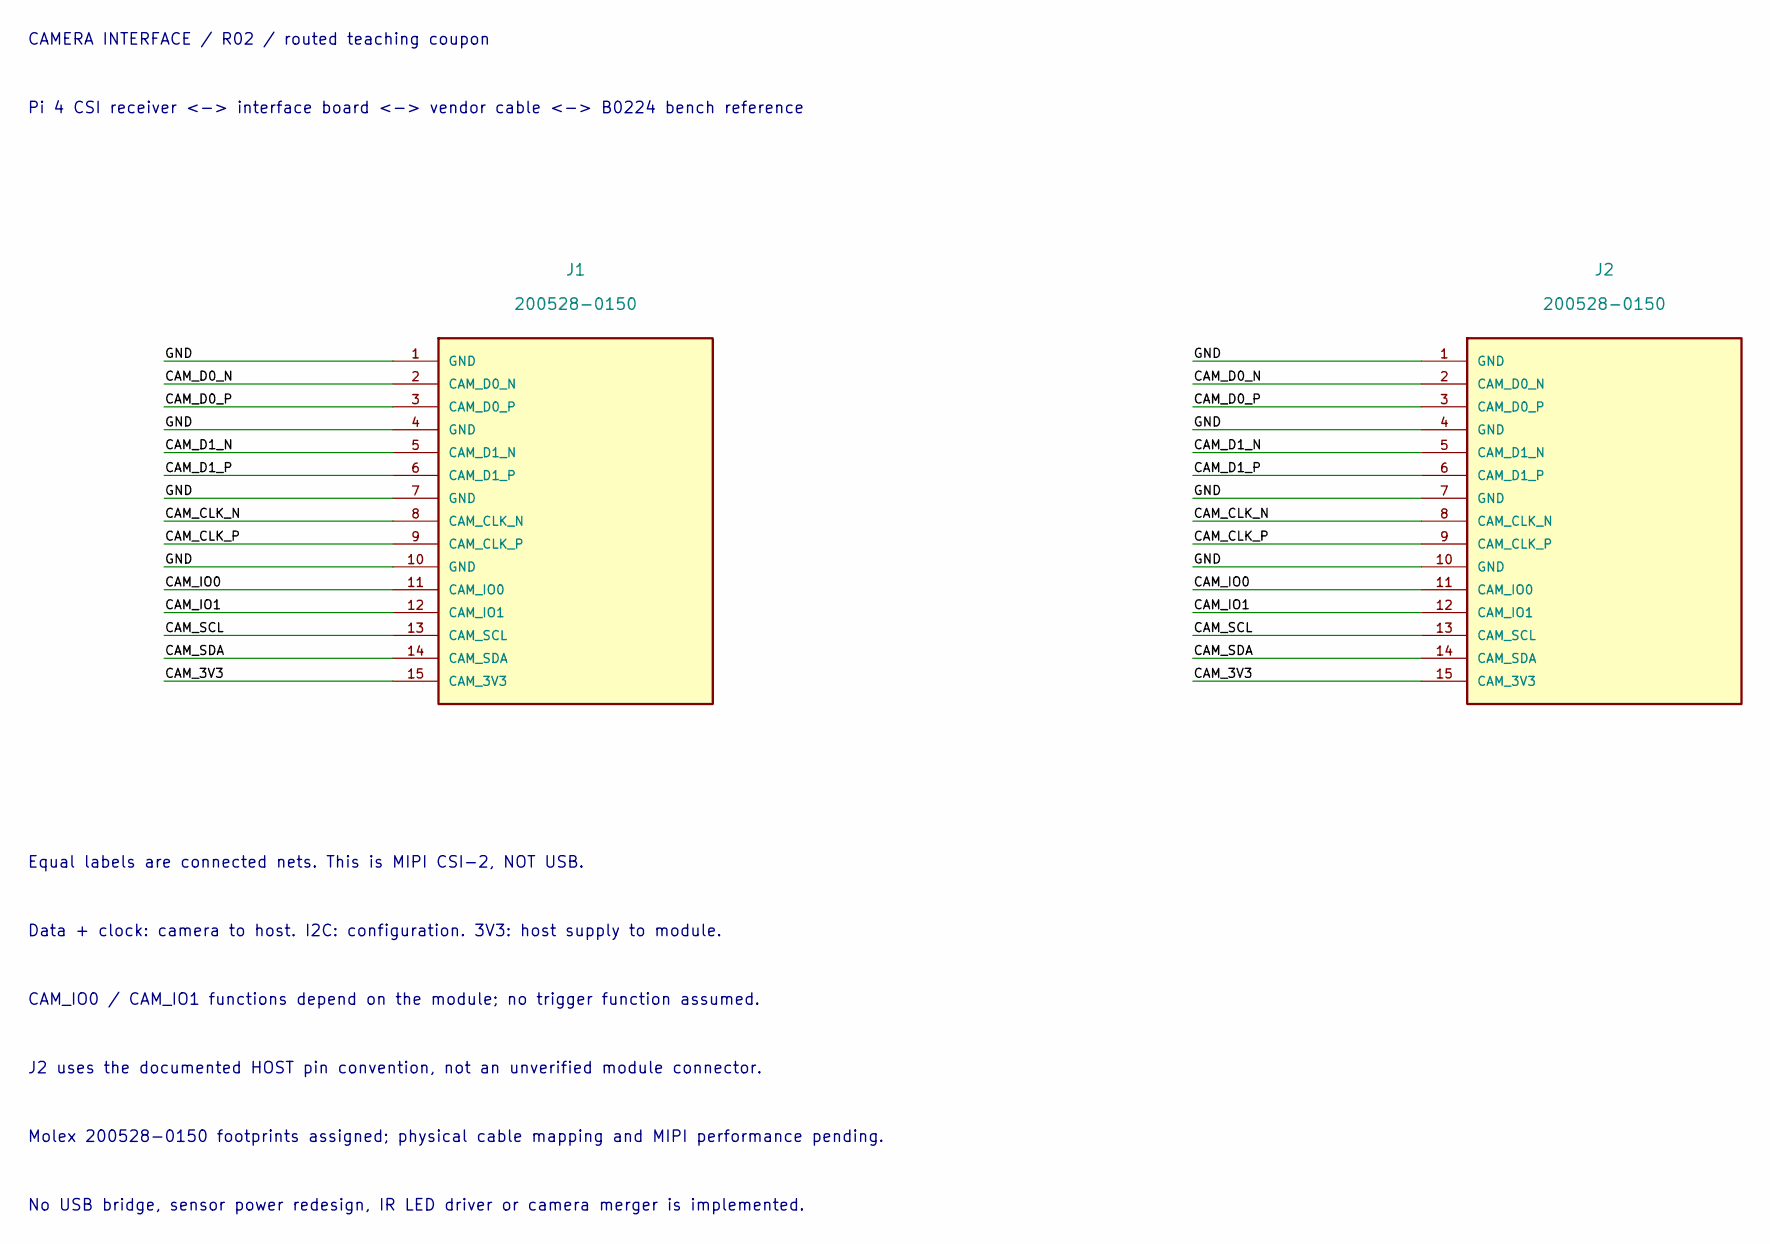
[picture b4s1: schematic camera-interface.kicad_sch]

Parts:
J1, J2: 200528-0150; Molex_200528-0150_1x15-1MP_P1.00mm_Horizontal

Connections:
/CAM_3V3: J1.15 (CAM_3V3), J2.15 (CAM_3V3)
/CAM_CLK_N: J1.8 (CAM_CLK_N), J2.8 (CAM_CLK_N)
/CAM_CLK_P: J1.9 (CAM_CLK_P), J2.9 (CAM_CLK_P)
/CAM_D0_N: J1.2 (CAM_D0_N), J2.2 (CAM_D0_N)
/CAM_D0_P: J1.3 (CAM_D0_P), J2.3 (CAM_D0_P)
/CAM_D1_N: J1.5 (CAM_D1_N), J2.5 (CAM_D1_N)
/CAM_D1_P: J1.6 (CAM_D1_P), J2.6 (CAM_D1_P)
/CAM_IO0: J1.11 (CAM_IO0), J2.11 (CAM_IO0)
/CAM_IO1: J1.12 (CAM_IO1), J2.12 (CAM_IO1)
/CAM_SCL: J1.13 (CAM_SCL), J2.13 (CAM_SCL)
/CAM_SDA: J1.14 (CAM_SDA), J2.14 (CAM_SDA)
/GND: J1.1 (GND), J1.4 (GND), J1.7 (GND), J1.10 (GND), J2.1 (GND), J2.4 (GND), J2.7 (GND), J2.10 (GND)

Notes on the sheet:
CAMERA INTERFACE / R02 / routed teaching coupon
Pi 4 CSI receiver <-> interface board <-> vendor cable <-> B0224 bench reference
Equal labels are connected nets. This is MIPI CSI-2, NOT USB.
Data + clock: camera to host. I2C: configuration. 3V3: host supply to module.
CAM_IO0 / CAM_IO1 functions depend on the module; no trigger function assumed.
J2 uses the documented HOST pin convention, not an unverified module connector.
Molex 200528-0150 footprints assigned; physical cable mapping and MIPI performance pending.
No USB bridge, sensor power redesign, IR LED driver or camera merger is implemented.

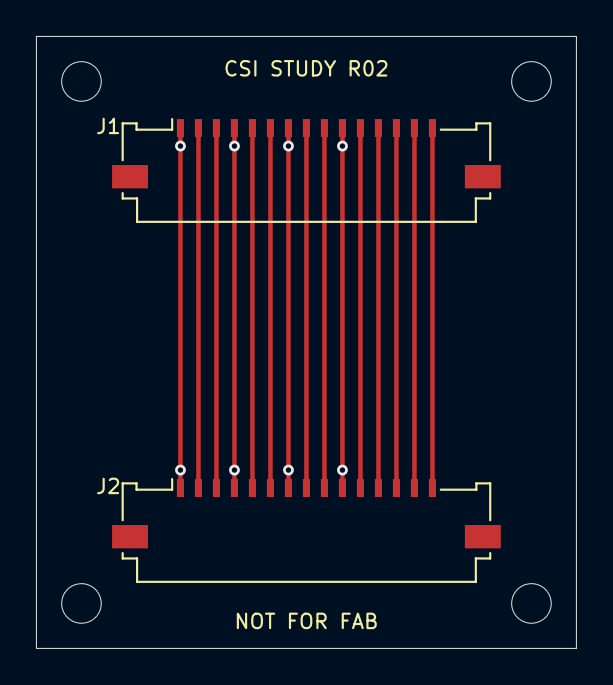
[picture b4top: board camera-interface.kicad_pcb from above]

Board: 2 copper layers, 30.0 x 34.0 mm, 6 parts (0 on the bottom side), 12 nets.

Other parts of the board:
H1, H2, H3, H4: (no value)

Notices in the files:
designs/eye-camera-ov9281/build_r02.py:
library names localized','kicad_libraries':'Installed KiCad 10.0.7; CC-BY-SA-4.0 with design exception','espressif_library':'CC-BY-SA-4.0 with design exception; see included license','antmicro':'Apache-2.0; copyright Antmicro 2019-2025','status':'Connected draft; schematic and BOM validation incompl
parts and their libraries:
License: Apache-2.0
